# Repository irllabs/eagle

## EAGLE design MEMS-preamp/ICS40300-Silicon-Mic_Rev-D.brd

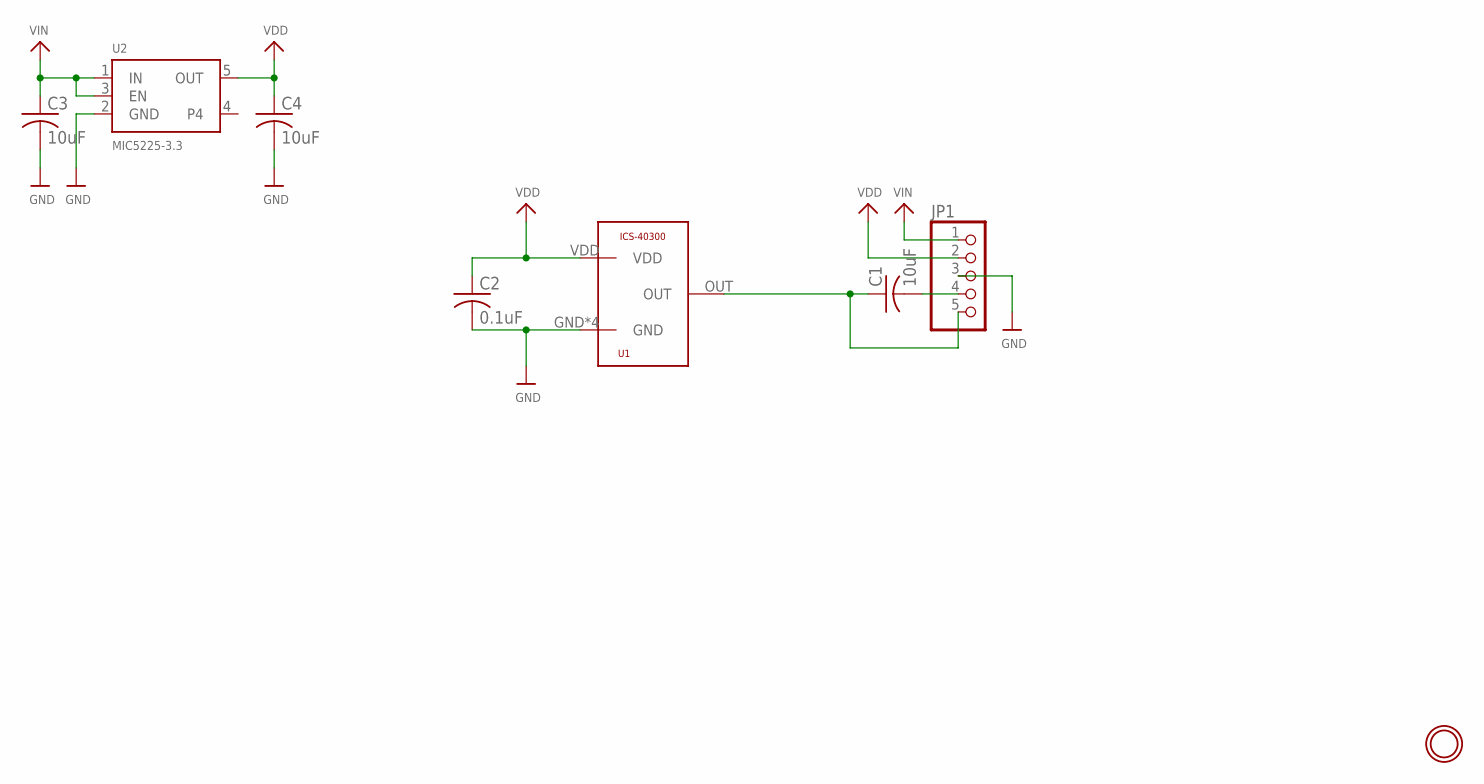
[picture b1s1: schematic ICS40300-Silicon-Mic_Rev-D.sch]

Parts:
C1, C3, C4: 10uF; C0805K
C2: 0.1uF; C0805K
JP1: HEADER-1X576MIL; 1X05_ROUND_76
U1: ICS-40300
U2: MIC5225-3.3; SOT23-5
U$12: MOUNTINGHOLE2.5; MOUNTINGHOLE_2.5_PLATED

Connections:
GND: C2.2, C3.2, C4.2, JP1.3, U1.GND, U1.GND1 (GND), U1.GND2 (GND), U1.GND3 (GND), U2.2 (GND)
unnamed: C1.1, JP1.5, U1.OUT
unnamed: C1.2, JP1.4
VDD: C2.1, C4.1, JP1.2, U1.VDD, U2.5 (OUT)
VIN: C3.1, JP1.1, U2.1 (IN), U2.3 (EN)

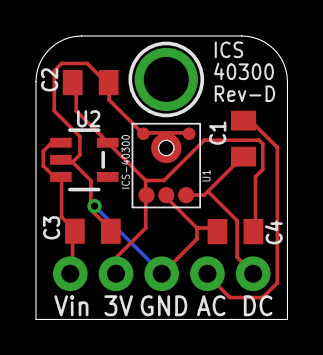
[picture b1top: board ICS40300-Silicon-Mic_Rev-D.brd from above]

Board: 2 copper layers, 14.0 x 15.7 mm, 8 parts (0 on the bottom side), 5 nets.

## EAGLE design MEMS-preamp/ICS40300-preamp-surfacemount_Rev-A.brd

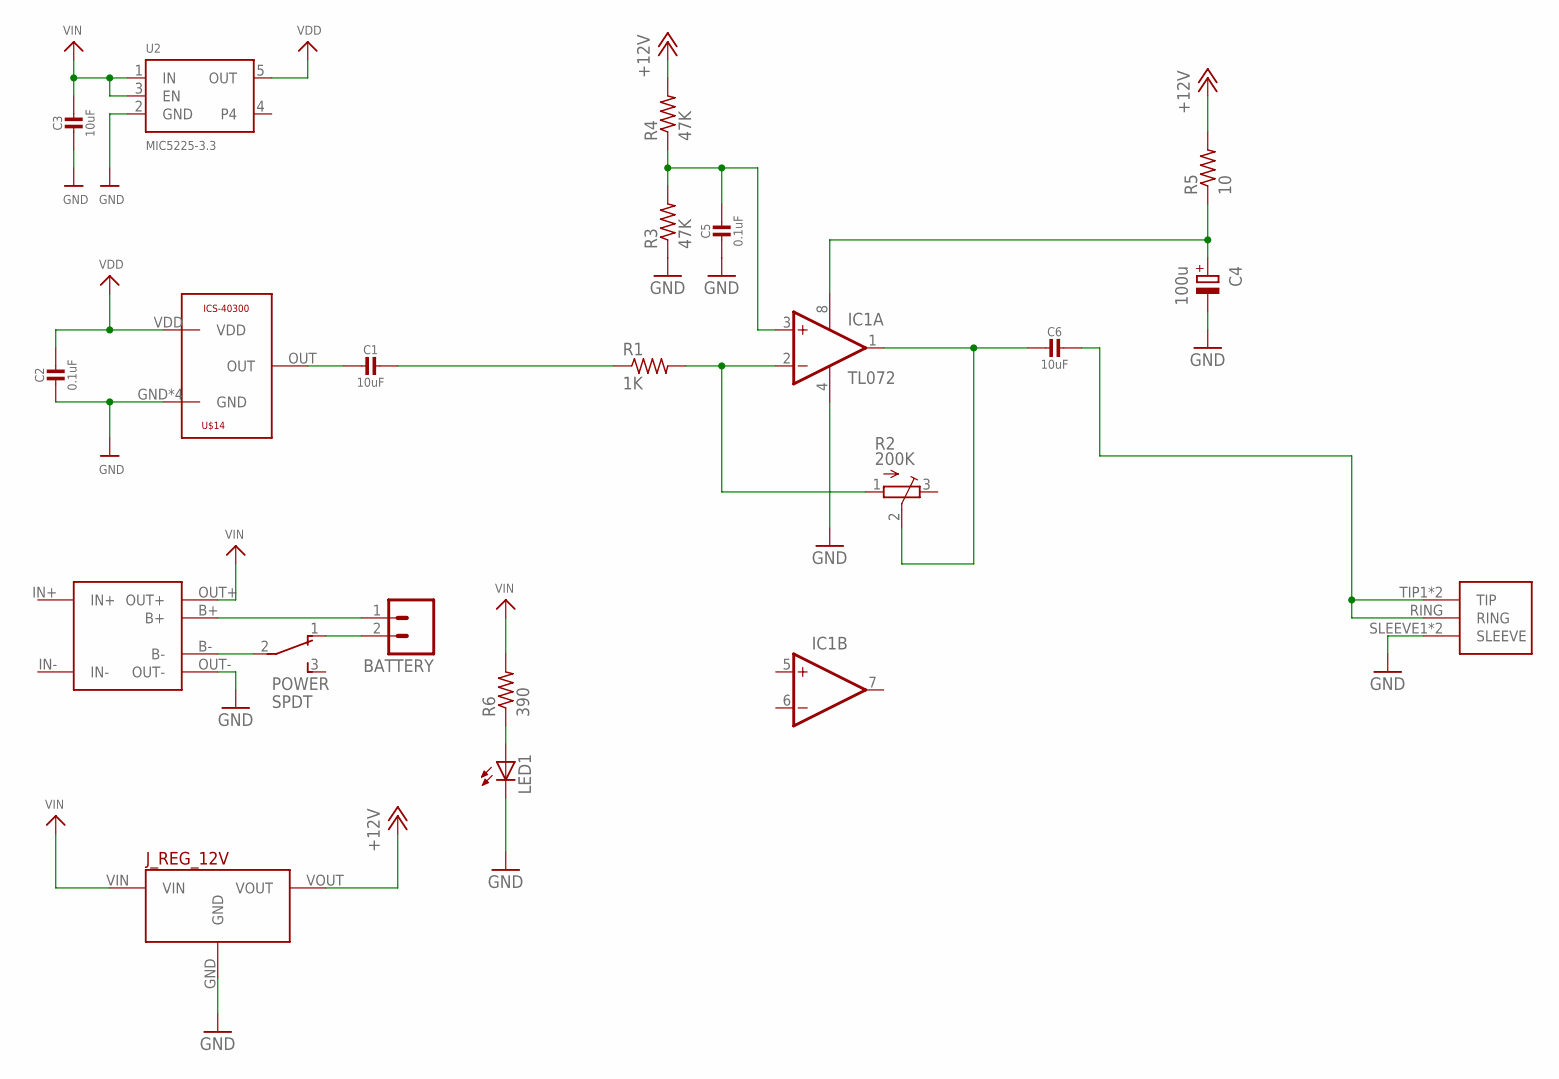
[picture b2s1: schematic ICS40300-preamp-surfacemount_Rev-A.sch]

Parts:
BATTERY: M02LOCK; 1X02_LOCK
C1, C3, C6: 10uF; 0805-NO
C2, C5: 0.1uF; 0805-NO
C4: 100u; TT2D4L
IC1: TL072; SO08
J_REG_12V: POLOLU_VOLTAGE_REGULATORS_3PIN; POLOLU_5V-12V_STEPUP_U3V12F5-U3V12F12
LED1: LED3MM
POWER: SPDT; SWITCH_SPDT-TE-CONNECT
R1: 1K; R0805
R2: 200K; TRIM-3386
R3, R4: 47K; R0805
R5: 10; R0805
R6: 390; R0805
U2: MIC5225-3.3; SOT23-5
U$13: 1/8"-F-STEREO-PCB
U$14: ICS-40300
USB-LIPO-CHARGER: TP4056-MODULE; TP4056-LITHIUM-PROTECTED-MODULE

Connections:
+12V: J_REG_12V.VOUT, R4.2, R5.2
GND: C2.2, C3.2, C4.-, C5.2, IC1.4 (V-), J_REG_12V.GND, LED1.K (C), R3.1, U2.2 (GND), U$13.SLEEVE1 (SLEEVE), U$13.SLEEVE2 (SLEEVE), U$14.GND, U$14.GND1 (GND), U$14.GND2 (GND), U$14.GND3 (GND), USB-LIPO-CHARGER.OUT-
IN+: USB-LIPO-CHARGER.IN+
IN-: USB-LIPO-CHARGER.IN-
unnamed: C1.2, U$14.OUT
unnamed: C1.1, R1.1
unnamed: C4.+, IC1.8 (V+), R5.1
unnamed: IC1.2 (-IN), R1.2, R2.1 (A)
unnamed: C6.1, U$13.RING, U$13.TIP1 (TIP), U$13.TIP2 (TIP)
unnamed: C5.1, IC1.3 (+IN), R3.2, R4.1
unnamed: C6.2, IC1.1 (OUT), R2.2 (S)
unnamed: BATTERY.2, POWER.1
unnamed: LED1.A, R6.1
unnamed: BATTERY.1, USB-LIPO-CHARGER.B+
unnamed: POWER.2, USB-LIPO-CHARGER.B-
VDD: C2.1, U2.5 (OUT), U$14.VDD
VIN: C3.1, J_REG_12V.VIN, R6.2, U2.1 (IN), U2.3 (EN), USB-LIPO-CHARGER.OUT+

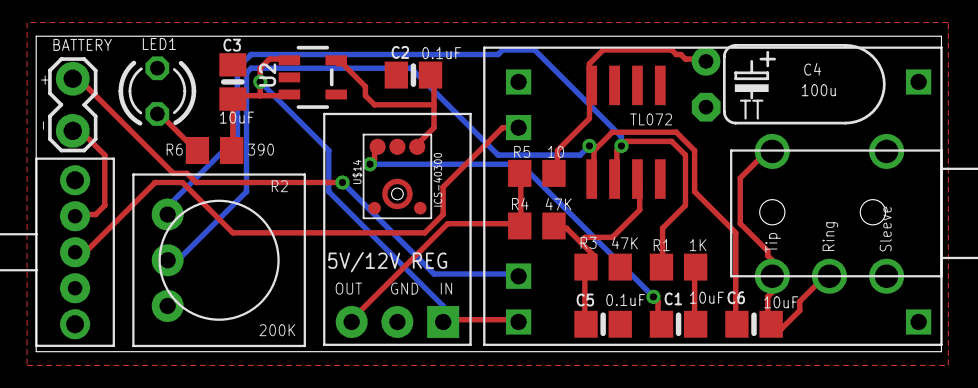
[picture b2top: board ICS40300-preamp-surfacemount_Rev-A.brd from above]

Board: 2 copper layers, 50.3 x 17.5 mm, 21 parts (0 on the bottom side), 15 nets.

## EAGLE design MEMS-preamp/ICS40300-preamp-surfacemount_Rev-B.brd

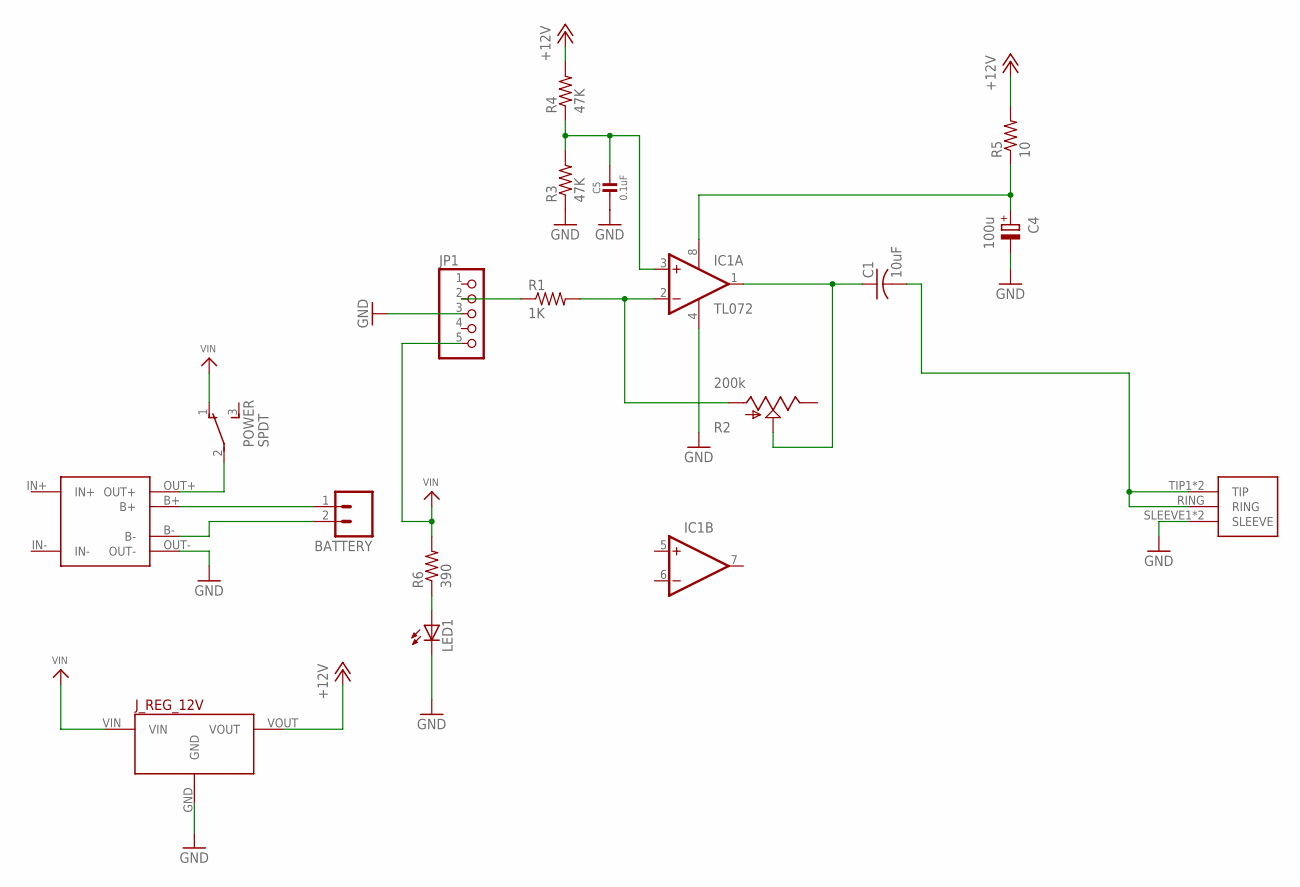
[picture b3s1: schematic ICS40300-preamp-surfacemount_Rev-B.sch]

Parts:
BATTERY: M02LOCK; 1X02_LOCK
C1: 10uF; C0805K
C4: 100u; TT2D4L
C5: 0.1uF; 0805-NO
IC1: TL072; SO08
JP1: HEADER-1X576MIL; 1X05_ROUND_76
J_REG_12V: POLOLU_VOLTAGE_REGULATORS_3PIN; POLOLU_5V-12V_STEPUP_U3V12F5-U3V12F12
LED1: LED3MM
POWER: SPDT; SWITCH_SPDT-TE-CONNECT
R1: 1K; R0805
R2: 200k; TRIMPOT-BOURNS-3306W
R3, R4: 47K; R0805
R5: 10; R0805
R6: 390; R0805
U$1: TP4056-MODULETP4056; TP4056-LITHIUM-PROTECTED-MODULE-MOVED-PAD
U$13: 1/8"-F-STEREO-PCB

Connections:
+12V: J_REG_12V.VOUT, R4.2, R5.2
GND: C4.-, C5.2, IC1.4 (V-), JP1.3, J_REG_12V.GND, LED1.K (C), R3.1, U$1.OUT-, U$13.SLEEVE1 (SLEEVE), U$13.SLEEVE2 (SLEEVE)
IN+: U$1.IN+
IN-: U$1.IN-
unnamed: JP1.2, R1.1
unnamed: IC1.2 (-IN), R1.2, R2.P$1 (IN)
unnamed: POWER.2, U$1.OUT+
unnamed: C4.+, IC1.8 (V+), R5.1
unnamed: BATTERY.1, U$1.B+
unnamed: BATTERY.2, U$1.B-
unnamed: C1.2, U$13.RING, U$13.TIP1 (TIP), U$13.TIP2 (TIP)
unnamed: C5.1, IC1.3 (+IN), R3.2, R4.1
unnamed: C1.1, IC1.1 (OUT), R2.P$2 (WIPER)
unnamed: LED1.A, R6.1
VIN: JP1.5, J_REG_12V.VIN, POWER.1, R6.2

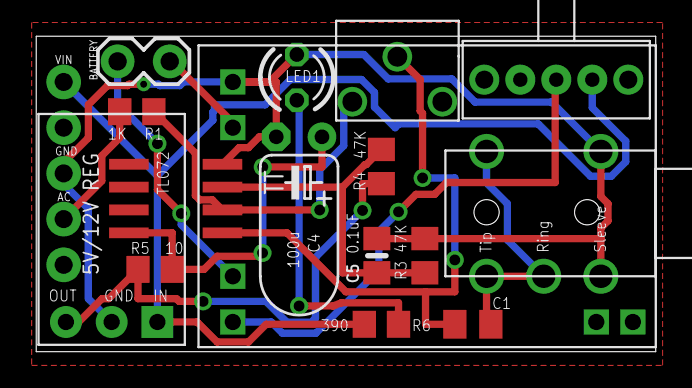
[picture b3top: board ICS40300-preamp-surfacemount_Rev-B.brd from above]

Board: 2 copper layers, 34.4 x 17.5 mm, 17 parts (0 on the bottom side), 13 nets.

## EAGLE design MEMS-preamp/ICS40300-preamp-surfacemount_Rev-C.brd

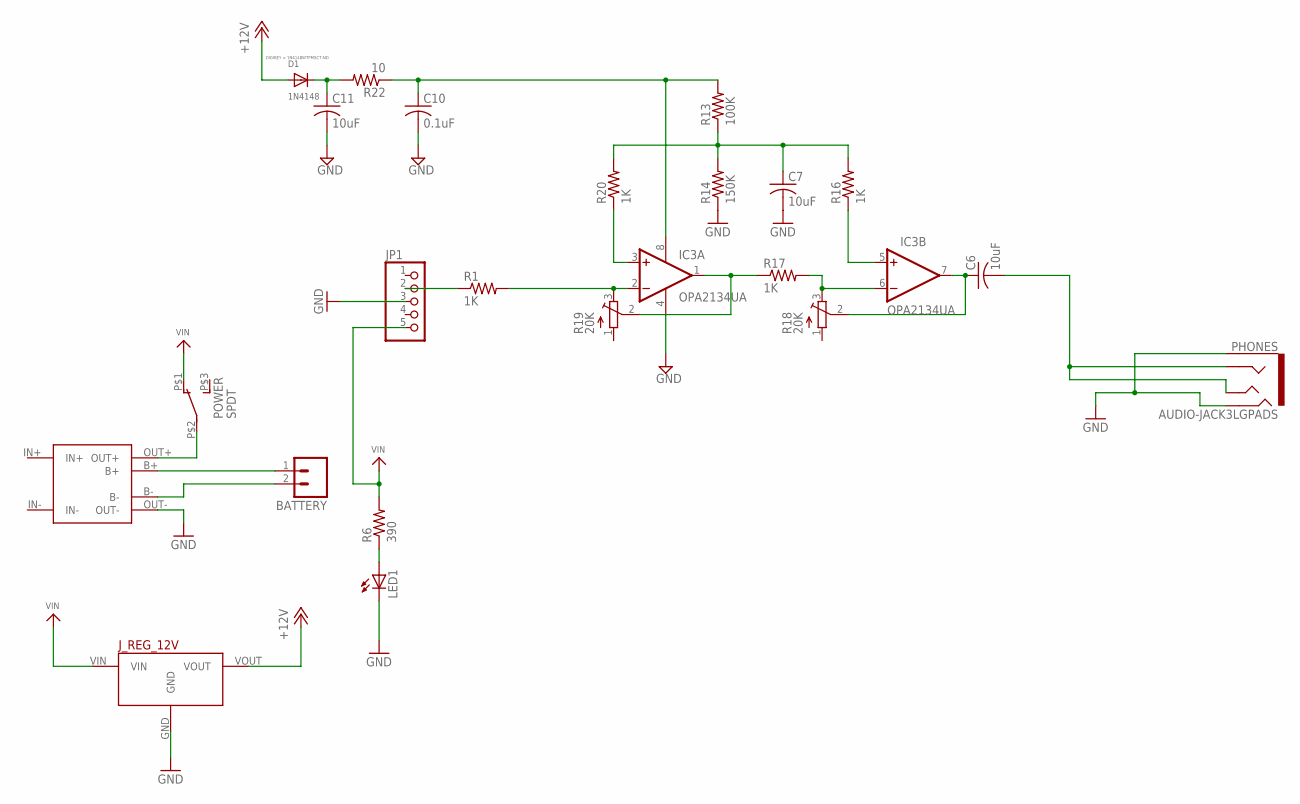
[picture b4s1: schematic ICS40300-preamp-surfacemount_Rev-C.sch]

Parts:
BATTERY: M02LOCK; 1X02_LOCK
C6, C7, C11: 10uF; C0805K
C10: 0.1uF; C0805K
D1: 1N4148; SOD-123; DIGIKEY 1N4148WTPMSCT-ND
IC3: OPA2134UA; SO08
JP1: HEADER-1X576MIL; 1X05_ROUND_76
J_REG_12V: POLOLU_VOLTAGE_REGULATORS_3PIN; POLOLU_5V-12V_STEPUP_U3V12F5-U3V12F12
LED1: LED3MM
PHONES: AUDIO-JACK3LGPADS; AUDIO-JACK-TRRS-SMD
POWER: SPDT; SWITCH_SPDT_CL-SB-12B
R1: 1K; R0805
R6: 390; R0805
R13: 100K; R0603
R14: 150K; R0603
R16, R17, R20: 1K; R0603
R18, R19: 20K; TC33X
R22: 10; R0603
U$1: TP4056-MODULETP4056; TP4056-LITHIUM-PROTECTED-MODULE-MOVED-PAD

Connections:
+12V: D1.A, J_REG_12V.VOUT
GND: C7.2, C10.2, C11.2, IC3.4 (V-), JP1.3, J_REG_12V.GND, LED1.K (C), PHONES.EARTH, PHONES.RING2, R14.1, U$1.OUT-
IN+: U$1.IN+
IN-: U$1.IN-
unnamed: JP1.2, R1.1
unnamed: POWER.P$2 (2), U$1.OUT+
unnamed: BATTERY.1, U$1.B+
unnamed: BATTERY.2, U$1.B-
unnamed: IC3.5 (+IN), R16.1
unnamed: C6.1, IC3.7 (OUT), R18.2 (S)
unnamed: IC3.6 (-IN), R17.2, R18.3 (E)
unnamed: LED1.A, R6.1
unnamed: C7.1, R13.1, R14.2, R16.2, R20.2
unnamed: IC3.3 (+IN), R20.1
unnamed: IC3.1 (OUT), R17.1, R19.2 (S)
unnamed: IC3.2 (-IN), R1.2, R19.3 (E)
unnamed: C6.2, PHONES.RING1, PHONES.TIP
unnamed: C11.1, D1.C, R22.2
unnamed: C10.1, IC3.8 (V+), R13.2, R22.1
VIN: JP1.5, J_REG_12V.VIN, POWER.P$1 (1), R6.2

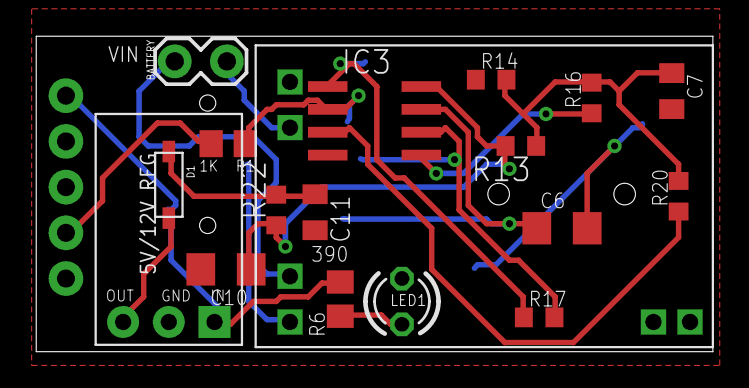
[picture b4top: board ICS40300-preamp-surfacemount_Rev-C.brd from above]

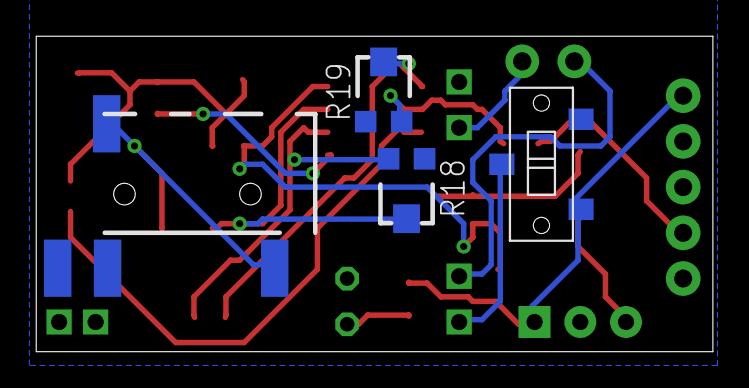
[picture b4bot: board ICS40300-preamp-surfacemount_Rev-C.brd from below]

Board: 2 copper layers, 37.6 x 17.5 mm, 23 parts (4 on the bottom side), 18 nets.

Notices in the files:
parts and their libraries:
microbuilder: This work is placed in the public domain, and may be freely used for commercial and non-commercial work with the following conditions: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
